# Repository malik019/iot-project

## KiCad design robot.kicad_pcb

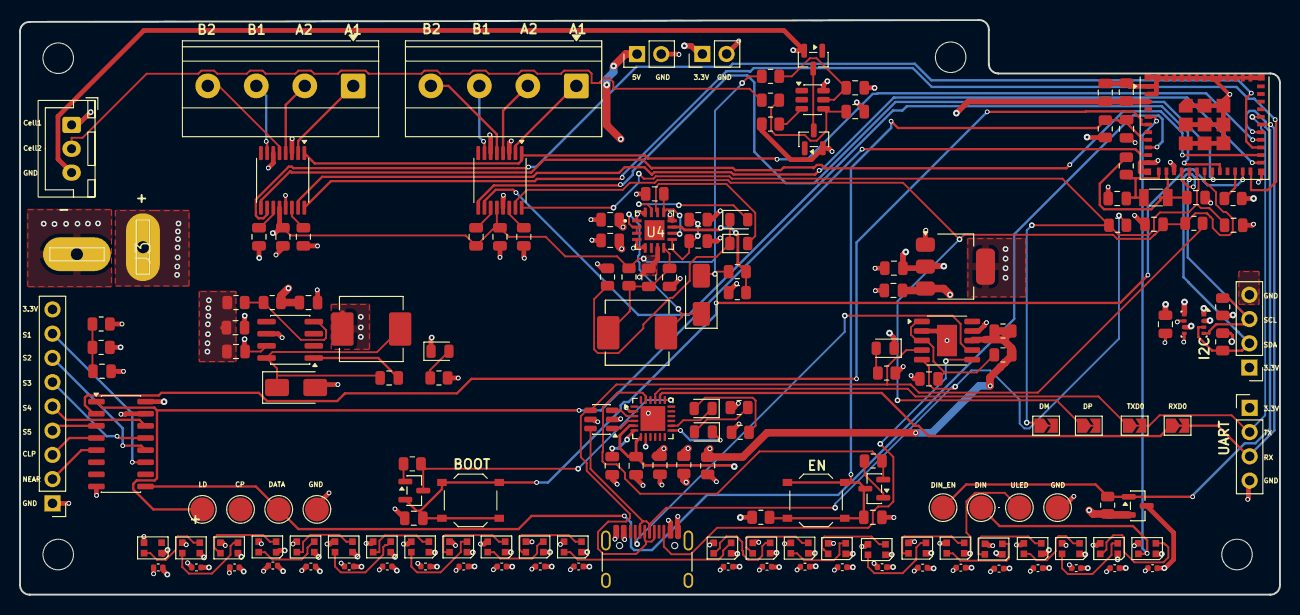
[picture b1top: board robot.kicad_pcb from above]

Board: 4 copper layers, 132.0 x 60.2 mm, 170 parts (0 on the bottom side), 107 nets.

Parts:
C1, C2, C4: 4.7uF; C_0805_2012Metric
C3, C16: O.1uF; C_0805_2012Metric
C5: 100uF; C_0805_2012Metric
C6: 47uF; C_0805_2012Metric
C7, C9, C10, C11, C12, C13, C14, C30, C33, C36: 10uF; C_0805_2012Metric
C8, C23, C25, C26, C27: 22uF; C_0805_2012Metric
C15, C31, C34: 100nF; C_0805_2012Metric
C17, C24: 0.1uF; C_0805_2012Metric
C18, C19, C20, C37, C38: 1uF; C_0805_2012Metric
C28, C29: 12pF; C_0805_2012Metric
C32, C35: 2.2uF; C_0805_2012Metric
C40, C41, C42, C43, C44, C45, C46, C47, C48, C49, C50, C51, C52, C53, C54, C55, C56, C57, C58, C59, C60, C61, C62, C63: 100nF; C_0402_1005Metric
D1, D6: SS32; D_SMA
D2, D8: Green; LED_0805_2012Metric
D3: Blue; LED_0805_2012Metric
D4, D5: Red; LED_0805_2012Metric
D7: Yellow; LED_0805_2012Metric
D10, D11, D12, D13, D14, D15, D16, D17, D18, D19, D20, D21, D22, D23, D24, D25, D26, D27, D28, D29, D30, D31, D32, D33: WS2812B; LED_WS2812B-2020_PLCC4_2.0x2.0mm
J1: USB_C_Receptacle_USB2.0_16P; USB_C_Receptacle_HRO_TYPE-C-31-M-12
J2: Batt-Cell Connector; JST_XH_B3B-XH-A_1x03_P2.50mm_Vertical
J3: Batt Connector; DEANS
J4: DVR FOUT; TerminalBlock_Phoenix_MKDS-1,5-4-5.08_1x04_P5.08mm_Horizont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
J5: 3.3V; PinHeader_1x02_P2.54mm_Vertical
J6: DRV BOUT; TerminalBlock_Phoenix_MKDS-1,5-4-5.08_1x04_P5.08mm_Horizont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
J7: UART; PinHeader_1x04_P2.54mm_Vertical
J8: I2C; PinHeader_1x04_P2.54mm_Vertical
J9: 5way Tracing; PinHeader_1x09_P2.54mm_Vertical
J10: 5V; PinHeader_1x02_P2.54mm_Vertical
JP1: TX; SolderJumper-2_P1.3mm_Open_TrianglePad1.0x1.5mm
JP2: RX; SolderJumper-2_P1.3mm_Open_TrianglePad1.0x1.5mm
JP3: USB_DP; SolderJumper-2_P1.3mm_Open_TrianglePad1.0x1.5mm
JP4: USB_DM; SolderJumper-2_P1.3mm_Open_TrianglePad1.0x1.5mm
L1, L2: 22uH; L_Changjiang_FXL0630
MH1, MH2, MH3, MH4: M3; MountingHole_3.2mm_M3
Q1, Q2: AO3400A; SOT-23
Q3, Q4: MMBT2222A; SOT-23
Q5: AO3401A; SOT-23
R1, R5: 1KΩ; R_0805_2012Metric
R2, R10, R21, R22, R24, R25, R30, R31, R32: 10kΩ; R_0805_2012Metric
R3: 1kΩ; R_0805_2012Metric
R4: 3k24Ω; R_0805_2012Metric
R6: 500Ω; R_0805_2012Metric
R7, R12, R13, R18: 330Ω; R_0805_2012Metric
R8: 0.5Ω; R_0805_2012Metric
R9: 20kΩ; R_0805_2012Metric
R11: 10KΩ; R_0805_2012Metric
R14: 2kΩ; R_0805_2012Metric
R15: 22K1Ω; R_0805_2012Metric
R16: 47K5Ω; R_0805_2012Metric
R17: 333Ω; R_0805_2012Metric
R19: 1OKΩ; R_0805_2012Metric
R23: 10k; R_0805_2012Metric
R26, R27: 47kΩ; R_0805_2012Metric
SW1: BOOT; SW_Push_1P1T_XKB_TS-1187A
SW2: EN; SW_Push_1P1T_XKB_TS-1187A
TH1: Thermistor_NTC; R_0805_2012Metric
TP1, TP2, TP3, TP4, TP5, TP6, TP7, TP8: TestPoint; TestPoint_Pad_D2.5mm
U1: TPS5420D; SOIC-8_3.9x4.9mm_P1.27mm
U2: CH224K; SSOP-10-1EP_3.9x4.9mm_P1mm_EP2.1x3.3mm
U3: AMS1117-3.3; SOT-223-3_TabPin2
U4: TP5100; QFN65P400X400X90-17N
U5: HY2120-CB; SOT-23-6
U6: USBLC6-2SC6; SOT-23-6
U7: CH9102F; QFN-24-1EP_4x4mm_P0.5mm_EP2.6x2.6mm
U8: ESP32-C6-MINI-1
U9, U11: DRV8833PW; TSSOP-16_4.4x5mm_P0.65mm
U10: 74HC165; SO-16_3.9x9.9mm_P1.27mm
U12: BME280; Bosch_LGA-8_2.5x2.5mm_P0.65mm_ClockwisePinNumbering
Y1: Crystal; Crystal_SMD_3215-2Pin_3.2x1.5mm

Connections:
+3.3V: C8.1, C19.2, C23.2, C24.2, C36.1, D5.1 (K), J5.1, J7.1, J8.1, J9.9, R21.2, R25.2, R26.2, R27.2, R32.2, U3.2 (VO), U7.5 (VIO), U7.7 (VDD5), U8.3 (3V3), U10.16 (VCC), U12.2 (CSB), U12.6 (VDDIO), U12.8 (VDD)
+5V: C5.1, C6.1, D4.1 (K), J10.1, L1.2, Q5.2 (S), R3.1, R19.2, U3.3 (VI)
+BATT: C1.1, C2.1, C30.2, C31.1, C33.2, C34.1, D6.2 (A), J2.1, J3.2, R8.2, R9.1, R12.1, TH1.1, U1.7 (VIN), U9.12 (VM), U11.12 (VM)
/BAT: C11.1, C12.1, U4.9 (BAT)
/BATT_READ: C15.1, R9.2, R10.1
/CC1: J1.A5 (CC1), U2.7 (CC1)
/CC2: J1.B5 (CC2), U2.6 (CC2)
/CHRG: D3.2 (A), U4.15 (~CHRG)
/CS: R14.1, U5.3 (CS)
/CV-VREG: C7.1, U4.10 (VREG), U4.13 (CS)
/Cell2: J2.2, R13.1
/D+: J1.A6 (D+), J1.B6 (D+), R22.2, U2.4 (DP), U6.4 (I/O2)
/D-: J1.A7 (D-), J1.B7 (D-), R23.2, U2.5 (DM), U6.6 (I/O1)
/ESP32-C6-mini/BOOT: C37.2, Q4.2 (E), SW1.1, SW1.2, U8.23 (IO9)
/ESP32-C6-mini/B_AIN1: U8.24 (IO18), U11.16 (AIN1)
/ESP32-C6-mini/B_AIN2: U8.25 (IO19), U11.15 (AIN2)
/ESP32-C6-mini/B_AOUT1: J6.1, U11.2 (AOUT1)
/ESP32-C6-mini/B_AOUT2: J6.2, U11.4 (AOUT2)
/ESP32-C6-mini/B_BIN1: U8.26 (IO20), U11.9 (BIN1)
/ESP32-C6-mini/B_BIN2: U8.27 (IO21), U11.10 (BIN2)
/ESP32-C6-mini/B_BOUT1: J6.3, U11.7 (BOUT1)
/ESP32-C6-mini/B_BOUT2: J6.4, U11.5 (BOUT2)
/ESP32-C6-mini/CLK: U8.6 (IO3), U10.2 (CP)
/ESP32-C6-mini/CLP: J9.3, U10.4 (D5)
/ESP32-C6-mini/D+: C26.2, JP3.1 (A), JP3.2 (B), R22.1, U8.18 (IO13), U9.15 (AIN2)
/ESP32-C6-mini/D-: C27.2, JP4.1 (A), JP4.2 (B), R23.1, U8.17 (IO12), U9.16 (AIN1)
/ESP32-C6-mini/DATA: TP3.1 (1_1), U8.9 (IO4), U10.9 (Q7)
/ESP32-C6-mini/DIN: D10.4 (DIN), TP6.1 (1_1), U8.5 (IO2)
/ESP32-C6-mini/DIN_EN: Q5.1 (G), R19.1, TP5.1 (1_1), U8.29 (IO23)
/ESP32-C6-mini/DTR: Q3.2 (E), R30.2, U7.23 (~DTR)
/ESP32-C6-mini/EN: C25.2, C38.2, Q3.3 (C), R21.1, R32.1, SW2.1, SW2.2, U8.8 (EN)
/ESP32-C6-mini/F_AOUT1: J4.1, U9.2 (AOUT1)
/ESP32-C6-mini/F_AOUT2: J4.2, U9.4 (AOUT2)
/ESP32-C6-mini/F_BIN1: U8.19 (IO14), U9.9 (BIN1)
/ESP32-C6-mini/F_BIN2: U8.20 (IO15), U9.10 (BIN2)
/ESP32-C6-mini/F_BOUT1: J4.3, U9.7 (BOUT1)
/ESP32-C6-mini/F_BOUT2: J4.4, U9.5 (BOUT2)
/ESP32-C6-mini/GPIO0: C28.2, R24.2, U8.12 (IO0), Y1.1
/ESP32-C6-mini/GPIO1: C29.2, R24.1, U8.13 (IO1), Y1.2
/ESP32-C6-mini/GPIO8: R25.1, U8.22 (IO8)
/ESP32-C6-mini/LD: TP1.1 (1_1), U8.10 (IO5), U10.1 (~PL)
/ESP32-C6-mini/NEAR: J9.2, U10.5 (D6)
/ESP32-C6-mini/RTS: Q4.3 (C), R31.2, U7.19 (~RTS)
/ESP32-C6-mini/RXD0: J7.3, JP2.1 (A), JP2.2 (B), U7.20 (RXD), U8.30 (RXD0)
/ESP32-C6-mini/RXS: D8.1 (K), U7.13 (RXS/GPIO1)
/ESP32-C6-mini/S1: J9.8, U10.11 (D0)
/ESP32-C6-mini/S2: J9.7, U10.12 (D1)
/ESP32-C6-mini/S3: J9.6, U10.13 (D2)
/ESP32-C6-mini/S4: J9.5, U10.14 (D3)
/ESP32-C6-mini/S5: J9.4, U10.3 (D4)
/ESP32-C6-mini/SCL: J8.3, R27.1, U8.16 (IO7), U12.4 (SCK)
/ESP32-C6-mini/SDA: J8.2, R26.1, U8.15 (IO6), U12.3 (SDI)
/ESP32-C6-mini/SLEEP: U8.28 (IO22), U9.1 (~SLEEP), U11.1 (~SLEEP)
/ESP32-C6-mini/TXD0: J7.2, JP1.1 (A), JP1.2 (B), U7.21 (TXD), U8.31 (TXD0)
/ESP32-C6-mini/TXS: D7.1 (K), U7.14 (TXS/GPIO0)
/ESP32-C6-mini/USB_D+: U6.3 (I/O2), U7.3 (D+)
/ESP32-C6-mini/USB_D-: U6.1 (I/O1), U7.4 (D-)
/ESP32-C6-mini/V3: C20.2, U7.6 (V3)
/ESP32-C6-mini/sensors/B_VCP: C34.2, U11.11 (VCP)
/ESP32-C6-mini/sensors/B_VINT: C35.1, U11.14 (VINT)
/ESP32-C6-mini/sensors/F_VCP: C31.2, U9.11 (VCP)
/ESP32-C6-mini/sensors/F_VINT: C32.1, U9.14 (VINT)
/ESP32-C6-mini/user_interface/ULED: C40.1, C41.1, C42.1, C43.1, C44.1, C45.1, C46.1, C47.1, C48.1, C49.1, C50.1, C51.1, C52.1, C53.1, C54.1, C55.1, C56.1, C57.1, C58.1, C59.1, C60.1, C61.1, C62.1, C63.1, D10.1 (VDD), D11.1 (VDD), D12.1 (VDD), D13.1 (VDD), D14.1 (VDD), D15.1 (VDD), D16.1 (VDD), D17.1 (VDD), D18.1 (VDD), D19.1 (VDD), D20.1 (VDD), D21.1 (VDD), D22.1 (VDD), D23.1 (VDD), D24.1 (VDD), D25.1 (VDD), D26.1 (VDD), D27.1 (VDD), D28.1 (VDD), D29.1 (VDD), D30.1 (VDD), D31.1 (VDD), D32.1 (VDD), D33.1 (VDD), Q5.3 (D), TP7.1 (1_1)
/LX: D6.1 (K), L2.1, U4.2 (LX), U4.3 (LX)
/STDBY: D2.2 (A), U4.14 (~STDBY)
/TS: R11.1, TH1.2, U4.11 (TS)
/VC: C17.1, R13.2, U5.4 (VC)
/VS: C13.1, C14.1, L2.2, R8.1, U4.8 (VS)
/VSNS: R3.2, R4.1, U1.4 (VSNS)
GND: C1.2, C2.2, C3.1, C5.2, C6.2, C7.2, C8.2, C9.2, C10.2, C11.2, C12.2, C13.2, C14.2, C15.2, C18.1, C19.1, C20.1, C23.1, C24.1, C25.1, C26.1, C27.1, C28.1, C29.1, C30.1, C32.2, C33.1, C35.2, C36.2, C37.1, C38.1, C40.2, C41.2, C42.2, C43.2, C44.2, C45.2, C46.2, C47.2, C48.2, C49.2, C50.2, C51.2, C52.2, C53.2, C54.2, C55.2, C56.2, C57.2, C58.2, C59.2, C60.2, C61.2, C62.2, C63.2, D1.2 (A), D10.3 (VSS), D11.3 (VSS), D12.3 (VSS), D13.3 (VSS), D14.3 (VSS), D15.3 (VSS), D16.3 (VSS), D17.3 (VSS), D18.3 (VSS), D19.3 (VSS), D20.3 (VSS), D21.3 (VSS), D22.3 (VSS), D23.3 (VSS), D24.3 (VSS), D25.3 (VSS), D26.3 (VSS), D27.3 (VSS), D28.3 (VSS), D29.3 (VSS), D30.3 (VSS), D31.3 (VSS), D32.3 (VSS), D33.3 (VSS), J1.A1 (GND), J1.A12 (GND), J1.B1 (GND), J1.B12 (GND), J3.1, J5.2, J7.4, J8.4, J9.1, J10.2, Q2.2 (S), R4.2, R6.2, R7.2, R10.2, R11.2, R14.2, R16.1, R17.2, R18.2, TP4.1 (1_1), TP8.1 (1_1), U1.6 (GND), U2.2 (CFG2), U2.9 (CFG1), U2.11 (GND), U3.1 (GND), U4.7 (GND), U4.12 (RTRICK), U6.2 (GND), U7.2 (GND), U7.25 (GND), U8.1 (GND), U8.2 (GND), U8.11 (GND), U8.14 (GND), U8.36 (GND), U8.37 (GND), U8.38 (GND), U8.39 (GND), U8.40 (GND), U8.41 (GND), U8.42 (GND), U8.43 (GND), U8.44 (GND), U8.45 (GND), U8.46 (GND), U8.47 (GND), U8.48 (GND), U8.49 (GND), U8.50 (GND), U8.51 (GND), U8.52 (GND), U8.53 (GND), U9.3 (AISEN), U9.6 (BISEN), U9.13 (GND), U10.8 (GND), U10.15 (~CE), U11.3 (AISEN), U11.6 (BISEN), U11.13 (GND), U12.1 (GND), U12.5 (SDO), U12.7 (GND)
GND1: C16.2, C17.2, J2.3, Q1.2 (S), U5.6 (VSS)
unnamed: C4.2, D1.1 (K), L1.1, U1.8 (PH)
unnamed: D2.1 (K), D3.1 (K), R5.2
unnamed: D4.2 (A), R6.1
unnamed: D5.2 (A), R7.1
unnamed: D7.2 (A), R17.1
unnamed: D8.2 (A), R18.1
unnamed: D10.2 (DOUT), D11.4 (DIN)
unnamed: D11.2 (DOUT), D12.4 (DIN)
unnamed: D12.2 (DOUT), D13.4 (DIN)
unnamed: D13.2 (DOUT), D14.4 (DIN)
unnamed: D14.2 (DOUT), D15.4 (DIN)
unnamed: D15.2 (DOUT), D16.4 (DIN)
unnamed: D16.2 (DOUT), D17.4 (DIN)
unnamed: D17.2 (DOUT), D18.4 (DIN)
unnamed: D18.2 (DOUT), D19.4 (DIN)
unnamed: D19.2 (DOUT), D20.4 (DIN)
unnamed: D20.2 (DOUT), D21.4 (DIN)
unnamed: D21.2 (DOUT), D22.4 (DIN)
unnamed: D22.2 (DOUT), D23.4 (DIN)
unnamed: D23.2 (DOUT), D24.4 (DIN)
unnamed: D24.2 (DOUT), D25.4 (DIN)
unnamed: D25.2 (DOUT), D26.4 (DIN)
unnamed: D26.2 (DOUT), D27.4 (DIN)
unnamed: D27.2 (DOUT), D28.4 (DIN)
unnamed: D28.2 (DOUT), D29.4 (DIN)
unnamed: D29.2 (DOUT), D30.4 (DIN)
unnamed: D30.2 (DOUT), D31.4 (DIN)
unnamed: D31.2 (DOUT), D32.4 (DIN)
unnamed: D32.2 (DOUT), D33.4 (DIN)
unnamed: Q1.3 (D), Q2.3 (D)
unnamed: Q3.1 (B), R30.1
unnamed: Q4.1 (B), R31.1
unnamed: C4.1, U1.1 (BOOT)
VBUS: C9.1, C10.1, C18.2, J1.A4 (VBUS), J1.A9 (VBUS), J1.B4 (VBUS), J1.B9 (VBUS), R1.2, R2.1, R2.2, R5.1, R15.1, R15.2, R16.2, U2.8 (VBUS), U4.1 (VIN), U4.4 (VIN), U4.5 (VIN), U4.16 (VIN), U6.5 (VBUS), U7.8 (VBUS)
VDD: C3.2, R1.1, U2.1 (VDD), U2.3 (CFG3)
VDDA: C16.1, R12.2, U5.5 (VDD)

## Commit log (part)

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2026-05-25 Add gerber file
2026-05-25 Update gerber file
2026-05-28 Refine PCB layout: shift status LED for better visibility
2026-06-10 add logboek documentation
2026-06-10 add firmware source code
2026-06-10 add performance visualization plots
2026-06-10 chore: add gitignore for KiCad and Office lock files
2026-06-10 update documentation
